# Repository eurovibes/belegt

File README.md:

<!-- SPDX-FileCopyrightText: 2025 Benedikt Spranger <b.spranger@linutronix.de> -->
<!-- SPDX-License-Identifier: CERN-OHL-S-2.0 -->

# Belegt - A model train track occupation sensor

## License rules

belegt is provided under the terms of the CERN-OHL-S license
version 2 as provided in the LICENSES/CERN-OHL-S-2.0 file.

Instead of adding license boilerplates to the individual files,
belegt uses SPDX license identifiers, which are machine parseable
and considered legaly equivalent.

The SPDX license identifier in belegt shall be added at the first
possible line in a file which can contain a comment. This is normally the
first line except for scripts. Scripts require the #!PATH_TO_INTERPRETER tag
in the first line; place the SPDX identifier into the second line.

The SPDX license identifier is added in form of a comment.

## Copyright and License

> Copyright Benedikt Spranger 2023.
> This source describes Open Hardware and is licensed under the CERNOHL-S v2.
> You may redistribute and modify this source and make products using it
> under the terms of the CERN-OHL-S v2 (https://ohwr.org/cern ohl s v2.txt ).
> This source is distributed WITHOUT ANY EXPRESS OR IMPLIED WARRANTY, INCLUDING
> OF MERCHANTABILITY, SATISFACTORY QUALITY AND FITNESS FOR A PARTICULAR PURPOSE.
> Please see the CERN-OHL-S v2 for applicable conditions.
> Source location: https://github.com/eurovibes/belegt
> As per CERN-OHL-S v2 section 4, should You produce hardware based
> on this source, You must where practicable maintain the Source Location
> visible on the external case of the belegt or other products you
> make using this source.

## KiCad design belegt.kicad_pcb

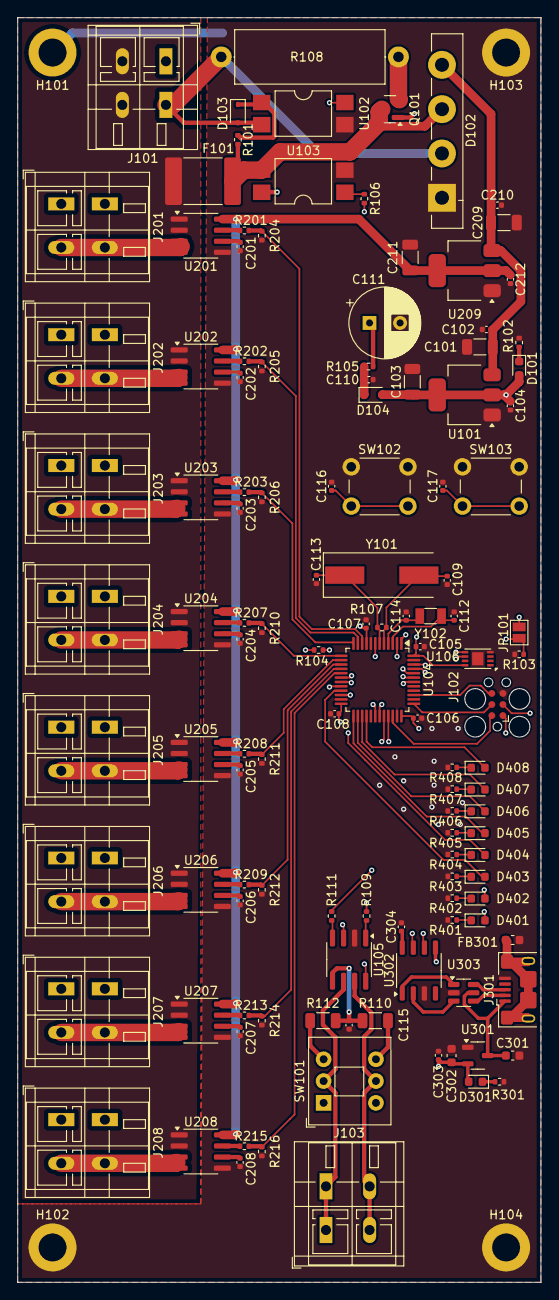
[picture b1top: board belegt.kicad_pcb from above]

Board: 4 copper layers, 60.0 x 145.0 mm, 126 parts (0 on the bottom side), 97 nets.

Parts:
C101, C103, C209, C211: 10µ; C_1206_3216Metric
C102, C104, C105, C106, C107, C108, C110, C116, C117, C201, C202, C203, C204, C205, C206, C207, C208, C210, C212, C303, C304: 100n; C_0402_1005Metric
C109, C113: 20p; C_0402_1005Metric
C111: 1F; CP_Radial_D8.0mm_P3.50mm
C112, C114: 12p; C_0402_1005Metric
C115: 4n7; C_0402_1005Metric
C301, C302: 1µ; C_0603_1608Metric
D101, D301, D401, D402, D403, D404, D405, D406, D407, D408: LED; LED_0603_1608Metric
D102: GBU8A; Diode_Bridge_Vishay_GBU
D103, D104: 1N4148WS; D_SOD-323
F101: Polyfuse_Small; Fuse_2920_7451Metric
FB301: FerriteBead_Small; L_0603_1608Metric
H101, H102, H103, H104: MountingHole_3.2mm_M3_ISO14580_Pad
J101: Power IN; TerminalBlock_WAGO_236-402_1x02_P5.00mm_45Degree
J102: Debug; Tag-Connect_TC2030-IDC-FP_2x03_P1.27mm_Vertical
J103: CAN; TerminalBlock_WAGO_236-402_1x02_P5.00mm_45Degree
J201: track1; TerminalBlock_WAGO_236-402_1x02_P5.00mm_45Degree
J202: track5; TerminalBlock_WAGO_236-402_1x02_P5.00mm_45Degree
J203: track7; TerminalBlock_WAGO_236-402_1x02_P5.00mm_45Degree
J204: track2; TerminalBlock_WAGO_236-402_1x02_P5.00mm_45Degree
J205: track6; TerminalBlock_WAGO_236-402_1x02_P5.00mm_45Degree
J206: track8; TerminalBlock_WAGO_236-402_1x02_P5.00mm_45Degree
J207: track3; TerminalBlock_WAGO_236-402_1x02_P5.00mm_45Degree
J208: track4; TerminalBlock_WAGO_236-402_1x02_P5.00mm_45Degree
J301: USB_B_Micro; USB_Micro-B_Amphenol_10118193-0001LF_Horizontal
JP101: Boot0; SolderJumper-2_P1.3mm_Open_Pad1.0x1.5mm
Q101: BC860; SOT-23
R101, R102, R104, R105, R106, R301, R401, R402, R403, R404, R405, R406, R407, R408: 1k; R_0402_1005Metric
R103, R204, R205, R206, R210, R211, R212, R214, R216: 10k; R_0402_1005Metric
R107: 1M; R_0402_1005Metric
R108: 100; R_Axial_DIN0617_L17.0mm_D6.0mm_P20.32mm_Horizontal
R109, R111: 100; R_0402_1005Metric
R110, R112: 60; R_1206_3216Metric
R201, R202, R203, R207, R208, R209, R213, R215: 2k; R_0402_1005Metric
SW101: Term; SW_Push_2P2T_Toggle_CK_PVA2xxH1xxxxxxV2
SW102: Reset; SW_PUSH_6mm
SW103: User; SW_PUSH_6mm
U101: AMS1117-3.3; SOT-223-3_TabPin2
U102, U103: EL817S1(C)(TU)-F; SMDIP-4_W9.53mm
U104: STM32F103CBTx; LQFP-48_7x7mm_P0.5mm
U105: TJA1042T; SOIC-8_3.9x4.9mm_P1.27mm
U106: ATECC608B-MAVDA-S; DFN-8-1EP_3x2mm_P0.5mm_EP1.3x1.5mm
U201, U202, U203, U204, U205, U206, U207, U208: ACS712ELCTR-05B; SOIC-8_3.9x4.9mm_P1.27mm
U209: AMS1117-5.0; SOT-223-3_TabPin2
U301: XC6206P332MR; SOT-23-3
U302: CH340N; SOP-8_3.9x4.9mm_P1.27mm
U303: USBLC6-2SC6; SOT-23-6
Y101: 8MHz; Crystal_SMD_HC49-SD
Y102: 32k; Crystal_SMD_3215-2Pin_3.2x1.5mm

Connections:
+3V3: C103.1, C104.1, C105.1, C106.1, C107.1, C108.1, D101.2 (A), D104.2 (A), J102.1 (VCC), JP101.2 (B), R104.2, U101.2 (VO), U104.9 (VDDA), U104.24 (VDD), U104.36 (VDD), U104.48 (VDD), U105.3 (VCC), U106.8 (VCC)
+5V: C211.1, C212.1, U201.8 (VCC), U202.8 (VCC), U203.8 (VCC), U204.8 (VCC), U205.8 (VCC), U206.8 (VCC), U207.8 (VCC), U208.8 (VCC), U209.2 (VO)
+15V: C101.1, C102.1, C209.1, C210.1, D102.4 (-), U101.3 (VI), U209.3 (VI)
+BATT: C111.1, R105.2, U104.1 (VBAT)
+VSW: F101.1, J101.2, U201.1 (IP+), U201.2 (IP+), U202.1 (IP+), U202.2 (IP+), U203.1 (IP+), U203.2 (IP+), U204.1 (IP+), U204.2 (IP+), U205.1 (IP+), U205.2 (IP+), U206.1 (IP+), U206.2 (IP+), U207.1 (IP+), U207.2 (IP+), U208.1 (IP+), U208.2 (IP+)
-VSW: D102.2, D103.2 (A), J101.1, J201.1, J202.1, J203.1, J204.1, J205.1, J206.1, J207.1, J208.1, R108.2, U102.2
/ACK: R106.1, U104.19 (PB1)
/BOOT0: JP101.1 (A), R103.1, U104.44 (BOOT0)
/BTN: C117.1, SW103.2, U104.2 (PC13)
/CAN_RX: R111.2, U104.33 (PA12)
/CAN_TX: R109.2, U104.32 (PA11)
/LED/LED1: D401.2 (A), U104.45 (PB8)
/LED/LED2: D402.2 (A), U104.46 (PB9)
/LED/LED3: D403.2 (A), U104.21 (PB10)
/LED/LED4: D404.2 (A), U104.22 (PB11)
/LED/LED5: D405.2 (A), U104.25 (PB12)
/LED/LED6: D406.2 (A), U104.26 (PB13)
/LED/LED7: D407.2 (A), U104.27 (PB14)
/LED/LED8: D408.2 (A), U104.28 (PB15)
/PROBE: R104.1, U102.4, U104.18 (PB0)
/SCL: U104.42 (PB6), U106.6 (SCL)
/SDA: U104.43 (PB7), U106.5 (SDA)
/SENSE0: R201.2, R204.2, U104.10 (PA0)
/SENSE1: R202.2, R205.2, U104.11 (PA1)
/SENSE2: R203.2, R206.2, U104.12 (PA2)
/SENSE3: R207.2, R210.2, U104.13 (PA3)
/SENSE4: R208.2, R211.2, U104.14 (PA4)
/SENSE5: R209.2, R212.2, U104.15 (PA5)
/SENSE6: R213.2, R214.2, U104.16 (PA6)
/SENSE7: R215.2, R216.2, U104.17 (PA7)
/STB: U104.20 (PB2), U105.8 (STB)
/SWCLK: J102.4 (SWCLK), U104.37 (PA14)
/SWDIO: J102.2 (SWDIO), U104.34 (PA13)
/SWO: J102.6 (SWO), U104.39 (PB3)
/Serial/RXD: U104.30 (PA9), U302.7 (RXD)
/Serial/TXD: U104.31 (PA10), U302.6 (TXD)
/~RST: C116.1, J102.3 (~RESET), SW102.2, U104.7 (NRST)
GND: C101.2, C102.2, C103.2, C104.2, C105.2, C106.2, C107.2, C108.2, C109.1, C110.2, C111.2, C112.1, C113.1, C114.1, C115.1, C116.2, C117.2, C201.2, C202.2, C203.2, C204.2, C205.2, C206.2, C207.2, C208.2, C209.2, C210.2, C211.2, C212.2, C301.2, C302.2, C303.2, C304.2, D102.1 (+), FB301.2, H101.1, H102.1, H103.1, H104.1, J102.5 (GND), J301.5 (GND), R102.2, R103.2, R204.1, R205.1, R206.1, R210.1, R211.1, R212.1, R214.1, R216.1, R301.1, R401.2, R402.2, R403.2, R404.2, R405.2, R406.2, R407.2, R408.2, SW102.1, SW103.1, U101.1 (GND), U102.3, U103.2, U104.8 (VSSA), U104.23 (VSS), U104.35 (VSS), U104.47 (VSS), U105.2 (GND), U106.4 (GND), U106.9 (EP), U201.5 (GND), U202.5 (GND), U203.5 (GND), U204.5 (GND), U205.5 (GND), U206.5 (GND), U207.5 (GND), U208.5 (GND), U209.1 (GND), U301.1 (GND), U302.3 (GND), U303.2 (GND)
unnamed: D101.1 (K), R102.1
unnamed: D103.1 (K), R101.1, U102.1
unnamed: C110.1, D104.1 (K), R105.1
unnamed: C302.1, C303.1, D301.2 (A), U301.2 (VO), U302.5 (VCC)
unnamed: D301.1 (K), R301.2
unnamed: D401.1 (K), R401.1
unnamed: D402.1 (K), R402.1
unnamed: D403.1 (K), R403.1
unnamed: D404.1 (K), R404.1
unnamed: D405.1 (K), R405.1
unnamed: D406.1 (K), R406.1
unnamed: D407.1 (K), R407.1
unnamed: D408.1 (K), R408.1
unnamed: J103.1, SW101.2 (B), U105.6 (CANL)
unnamed: J103.2, SW101.5 (B), U105.7 (CANH)
unnamed: J201.2, U201.3 (IP-), U201.4 (IP-)
unnamed: J202.2, U202.3 (IP-), U202.4 (IP-)
unnamed: J203.2, U203.3 (IP-), U203.4 (IP-)
unnamed: J204.2, U204.3 (IP-), U204.4 (IP-)
unnamed: J205.2, U205.3 (IP-), U205.4 (IP-)
unnamed: J206.2, U206.3 (IP-), U206.4 (IP-)
unnamed: J207.2, U207.3 (IP-), U207.4 (IP-)
unnamed: J208.2, U208.3 (IP-), U208.4 (IP-)
unnamed: J301.3 (D+), U303.6 (I/O1)
unnamed: J301.2 (D-), U303.4 (I/O2)
unnamed: FB301.1, J301.6 (Shield)
unnamed: C301.1, J301.1 (VBUS), U301.3 (VI), U303.5 (VBUS)
unnamed: Q101.1 (B), U103.4
unnamed: D102.3, F101.2, Q101.3 (C), R101.2, U103.3
unnamed: Q101.2 (E), R108.1
unnamed: R106.2, U103.1
unnamed: R110.1, SW101.6 (C)
unnamed: R112.2, SW101.3 (C)
unnamed: C112.2, U104.3 (PC14), Y102.2
unnamed: C114.2, U104.4 (PC15), Y102.1
unnamed: C109.2, R107.1, U104.5 (PD0), Y101.2
unnamed: C113.2, R107.2, U104.6 (PD1), Y101.1
unnamed: R111.1, U105.4 (RXD)
unnamed: C115.2, R110.2, R112.1, U105.5 (SPLIT)
unnamed: R109.1, U105.1 (TXD)
unnamed: C201.1, U201.6 (FILTER)
unnamed: R201.1, U201.7 (VIOUT)
unnamed: C202.1, U202.6 (FILTER)
unnamed: R202.1, U202.7 (VIOUT)
unnamed: C203.1, U203.6 (FILTER)
unnamed: R203.1, U203.7 (VIOUT)
unnamed: C204.1, U204.6 (FILTER)
unnamed: R207.1, U204.7 (VIOUT)
unnamed: C205.1, U205.6 (FILTER)
unnamed: R208.1, U205.7 (VIOUT)
unnamed: C206.1, U206.6 (FILTER)
unnamed: R209.1, U206.7 (VIOUT)
unnamed: C207.1, U207.6 (FILTER)
unnamed: R213.1, U207.7 (VIOUT)
unnamed: C208.1, U208.6 (FILTER)
unnamed: R215.1, U208.7 (VIOUT)
unnamed: U302.1 (UD+), U303.1 (I/O1)
unnamed: U302.2 (UD-), U303.3 (I/O2)
unnamed: C304.1, U302.8 (V3)

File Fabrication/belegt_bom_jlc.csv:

"Comment","Designator","Footprint","LCSC Part #"
"12p","C112,C114","C_0402_1005Metric","C1547"
"20p","C109,C113","C_0402_1005Metric","C1554"
"4n7","C115","C_0402_1005Metric","C1538"
"100n","C102,C104,C105,C106,C107,C108,C110,C116,C117,C201,C202,C203,C204,C205,C206,C207,C208,C210,C212,C303,C304","C_0402_1005Metric","C307331"
"1µ","C301,C302","C_0603_1608Metric","C15849"
"10µ","C101,C103,C209,C211","C_1206_3216Metric","C13585"
"1N4148WS","D103,D104","D_SOD-323","C2128"
"LED","D101,D301,D401,D402,D403,D404,D405,D406,D407,D408","LED_0603_1608Metric","C2286"
"Polyfuse_Small","F101","Fuse_2920_7451Metric","C495350"
"FerriteBead_Small","FB301","L_0603_1608Metric","C1002"
"USB_B_Micro","J301","USB_Micro-B_Amphenol_10118193-0001LF_Horizontal","C132562"
"BC860","Q101","SOT-23","C475637"
"60","R110,R112","R_1206_3216Metric","C57572"
"100","R109,R111","R_0402_1005Metric","C25076"
"1k","R101,R102,R104,R105,R106,R301,R401,R402,R403,R404,R405,R406,R407,R408","R_0402_1005Metric","C11702"
"2k","R201,R202,R203,R207,R208,R209,R213,R215","R_0402_1005Metric","C4109"
"10k","R103,R204,R205,R206,R210,R211,R212,R214,R216","R_0402_1005Metric","C25744"
"1M","R107","R_0402_1005Metric","C26083"
"ACS712ELCTR-05B","U201,U202,U203,U204,U205,U206,U207,U208","SOIC-8_3.9x4.9mm_P1.27mm","C44471"
"AMS1117-3.3","U101","SOT-223-3_TabPin2","C6186"
"AMS1117-5.0","U209","SOT-223-3_TabPin2","C6187"
"ATECC608B-MAVDA-S","U106","DFN-8-1EP_3x2mm_P0.5mm_EP1.3x1.5mm","C17350254"
"CH340N","U302","SOP-8_3.9x4.9mm_P1.27mm","C2977777"
"EL817S1(C)(TU)-F","U102,U103","SMDIP-4_W9.53mm","C106900"
"STM32F103CBTx","U104","LQFP-48_7x7mm_P0.5mm","C8304"
"TJA1042T","U105","SOIC-8_3.9x4.9mm_P1.27mm","C53670"
"USBLC6-2SC6","U303","SOT-23-6","C2827654"
"XC6206P332MR","U301","SOT-23-3","C5446"
"32k","Y102","Crystal_SMD_3215-2Pin_3.2x1.5mm","C32346"
"8MHz","Y101","Crystal_SMD_HC49-SD","C12674"

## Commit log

2025-02-18 Initial
2025-02-28 Add readme and license text
2025-02-28 Add logo
2025-02-28 Add github workflow
2025-02-28 Initial gh-pages commit
2025-02-28 Deploying to gh-pages from @ eurovibes/belegt@0f5465e367ad272f7ead5fe17ccb378918936b9e 🚀
